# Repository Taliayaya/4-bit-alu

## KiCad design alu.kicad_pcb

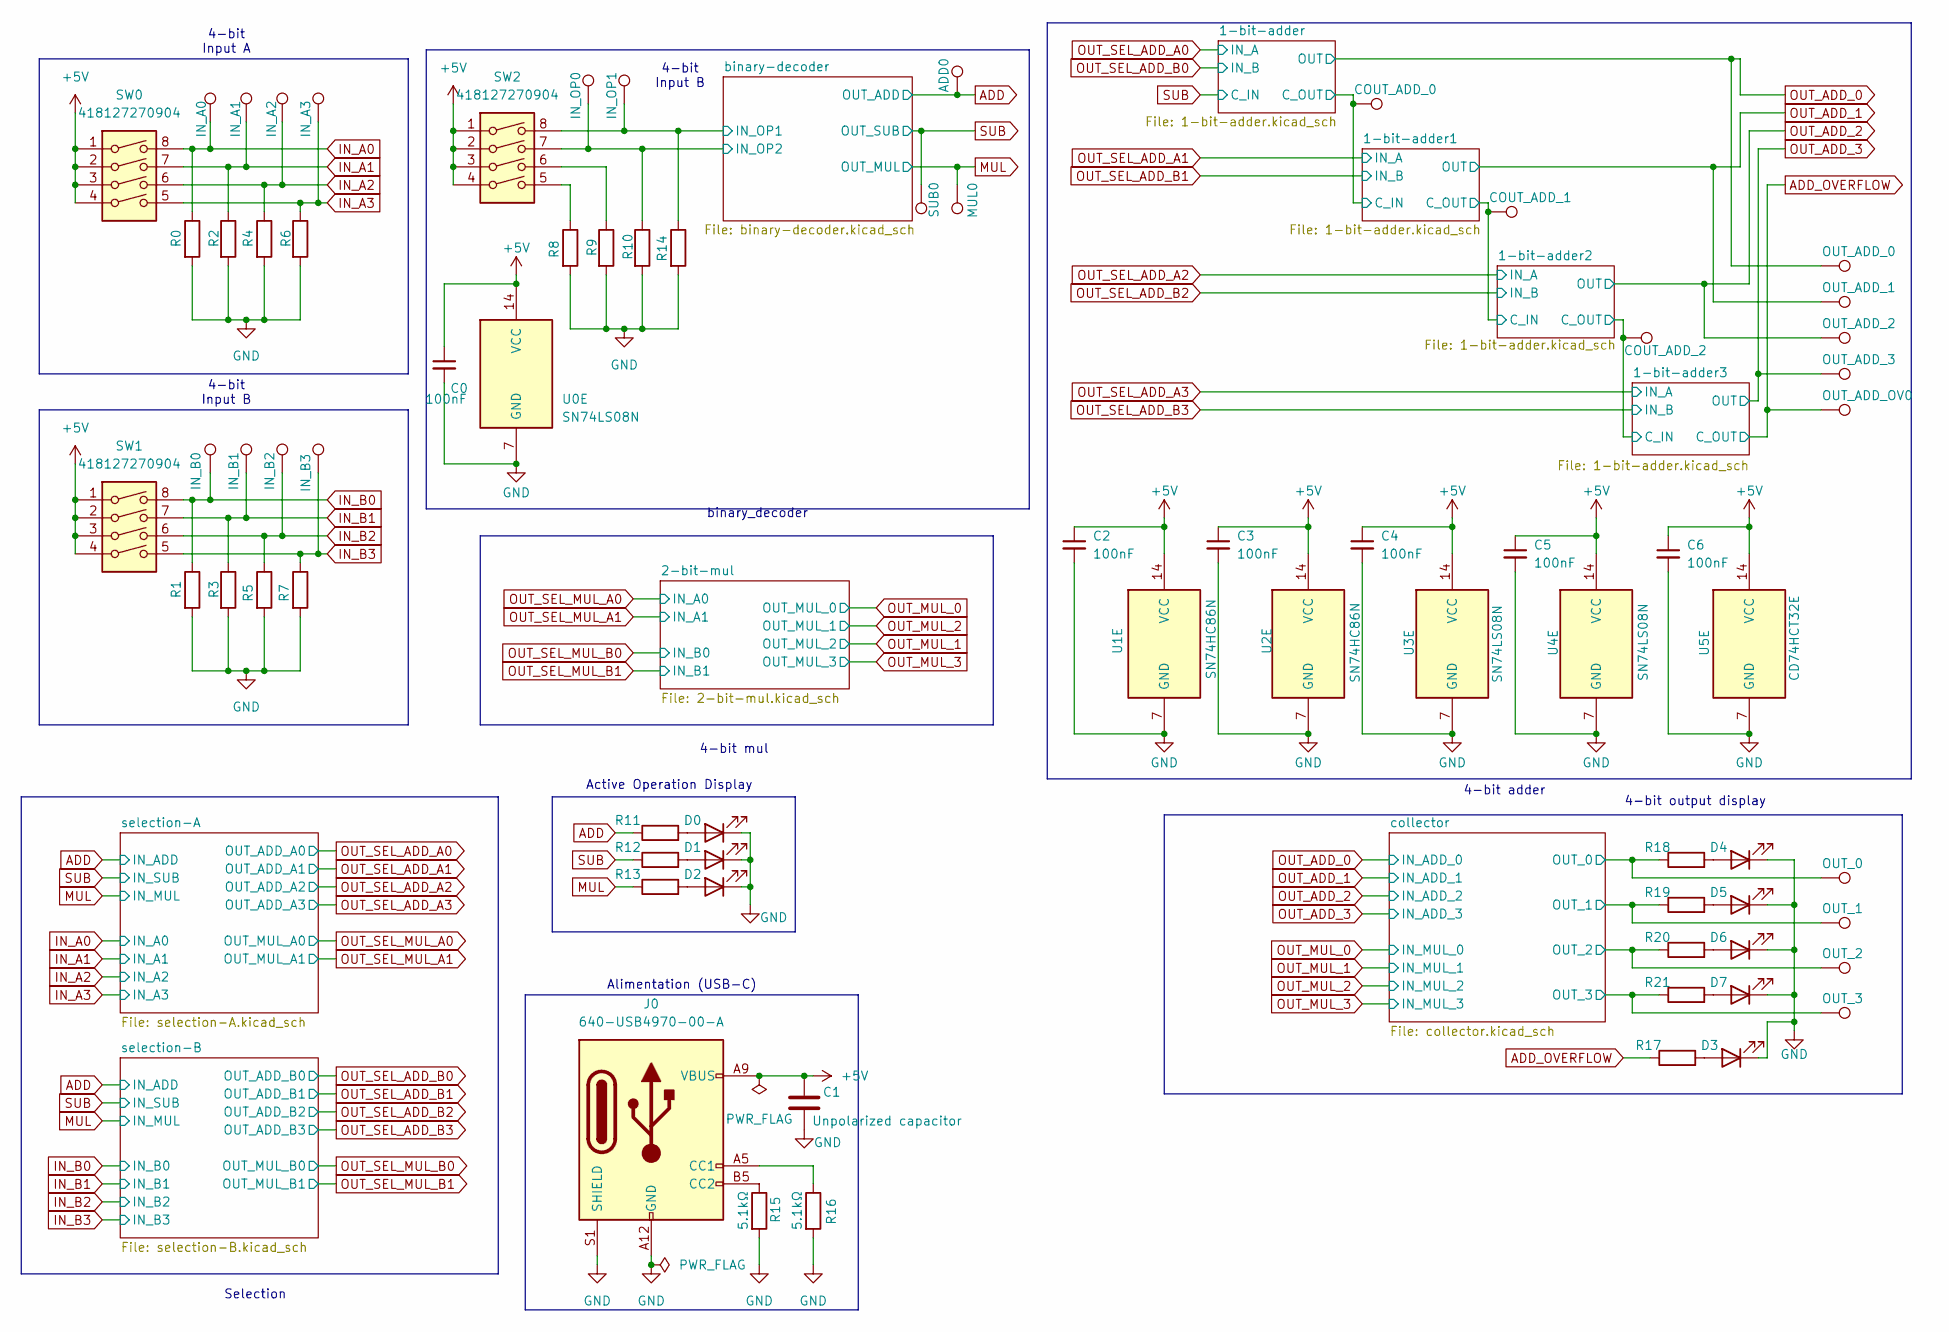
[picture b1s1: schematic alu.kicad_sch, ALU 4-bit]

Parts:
ADD0: TestPoint; TestPoint_THTPad_D1.0mm_Drill0.5mm
C0, C2, C3, C4, C5, C6: 100nF; C_0603_1608Metric
C1: 10uF; C_0603_1608Metric_Pad1.08x0.95mm_HandSolder
COUT_ADD_0, COUT_ADD_1, COUT_ADD_2: TestPoint; TestPoint_THTPad_D1.0mm_Drill0.5mm
D0, D1, D2, D3, D4, D5, D6, D7: 150080RS75000; LED_0805_2012Metric
IN_A0, IN_A1, IN_A2, IN_A3: TestPoint; TestPoint_THTPad_D1.0mm_Drill0.5mm
IN_B0, IN_B1, IN_B2, IN_B3: TestPoint; TestPoint_THTPad_D1.0mm_Drill0.5mm
IN_OP0, IN_OP1: TestPoint; TestPoint_THTPad_D1.0mm_Drill0.5mm
J0: 640-USB4970-00-A; USB_C_Receptacle_GCT_USB4125-xx-x_6P_TopMnt_Horizontal
MUL0: TestPoint; TestPoint_THTPad_D1.0mm_Drill0.5mm
OUT_0, OUT_1, OUT_2, OUT_3: TestPoint; TestPoint_THTPad_D1.0mm_Drill0.5mm
OUT_ADD_0, OUT_ADD_1, OUT_ADD_2, OUT_ADD_3: TestPoint; TestPoint_THTPad_D1.0mm_Drill0.5mm
OUT_ADD_OV0: TestPoint; TestPoint_THTPad_D1.0mm_Drill0.5mm
R0, R1, R2, R3, R4, R5, R6, R7, R8, R9, R10, R14: 10kΩ; R_0603_1608Metric_Pad0.98x0.95mm_HandSolder
R11, R12, R13, R17, R18, R19, R20, R21: 220Ω; R_0603_1608Metric_Pad0.98x0.95mm_HandSolder
R15, R16: 5.1kΩ; R_0603_1608Metric_Pad0.98x0.95mm_HandSolder
SUB0: TestPoint; TestPoint_THTPad_D1.0mm_Drill0.5mm
SW0, SW1, SW2: 418127270904; SW_DIP_SPSTx04_Slide_6.7x11.72mm_W7.62mm_P2.54mm_LowProfile
U0, U3, U4: SN74LS08N; DIP-14_W7.62mm_LongPads
U1, U2: SN74HC86N; DIP-14_W7.62mm_LongPads
U5: CD74HCT32E; DIP-14_W7.62mm_LongPads

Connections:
+5V: C0.1, C1.1, C2.1, C3.1, C4.1, C5.1, C6.1, J0.A9 (VBUS), J0.B9 (VBUS), SW0.1, SW0.2, SW0.3, SW0.4, SW1.1, SW1.2, SW1.3, SW1.4, SW2.1, SW2.2, SW2.3, SW2.4, U0.14 (VCC), U1.14 (VCC), U2.14 (VCC), U3.14 (VCC), U4.14 (VCC), U5.14 (VCC); also elsewhere on the board
/1-bit-adder1/C_OUT: COUT_ADD_1.1, U5.6; also elsewhere on the board
/1-bit-adder2/C_OUT: COUT_ADD_2.1, U2.13, U3.12, U5.8
/1-bit-adder/C_OUT: COUT_ADD_0.1, U0.12, U1.13; also elsewhere on the board
/binary-decoder/IN_OP1: IN_OP1.1, R14.1, SW2.8; also elsewhere on the board
/binary-decoder/IN_OP2: IN_OP0.1, R10.1, SW2.7; also elsewhere on the board
/collector/OUT_0: OUT_0.1, R18.1; also elsewhere on the board
/collector/OUT_1: OUT_1.1, R19.1; also elsewhere on the board
/collector/OUT_2: OUT_2.1, R20.1; also elsewhere on the board
/collector/OUT_3: OUT_3.1, R21.1; also elsewhere on the board
ADD: ADD0.1, R11.1; also elsewhere on the board
ADD_OVERFLOW: OUT_ADD_OV0.1, R17.1, U5.11
GND: C0.2, C1.2, C2.2, C3.2, C4.2, C5.2, C6.2, D0.1 (K), D1.1 (K), D2.1 (K), D3.1 (K), D4.1 (K), D5.1 (K), D6.1 (K), D7.1 (K), J0.A12 (GND), J0.B12 (GND), J0.S1 (SHIELD), R0.2, R1.2, R2.2, R3.2, R4.2, R5.2, R6.2, R7.2, R8.2, R9.2, R10.2, R14.2, R15.2, R16.2, U0.7 (GND), U1.7 (GND), U2.7 (GND), U3.7 (GND), U4.7 (GND), U5.7 (GND); also elsewhere on the board
IN_A0: IN_A0.1, R0.1, SW0.8; also elsewhere on the board
IN_A1: IN_A1.1, R2.1, SW0.7; also elsewhere on the board
IN_A2: IN_A2.1, R4.1, SW0.6; also elsewhere on the board
IN_A3: IN_A3.1, R6.1, SW0.5; also elsewhere on the board
IN_B0: IN_B0.1, R1.1, SW1.8; also elsewhere on the board
IN_B1: IN_B1.1, R3.1, SW1.7; also elsewhere on the board
IN_B2: IN_B2.1, R5.1, SW1.6; also elsewhere on the board
IN_B3: IN_B3.1, R7.1, SW1.5; also elsewhere on the board
MUL: MUL0.1, R13.1; also elsewhere on the board
unnamed: D0.2 (A), R11.2
unnamed: D1.2 (A), R12.2
unnamed: D2.2 (A), R13.2
unnamed: D3.2 (A), R17.2
unnamed: D4.2 (A), R18.2
unnamed: D5.2 (A), R19.2
unnamed: D6.2 (A), R20.2
unnamed: D7.2 (A), R21.2
unnamed: J0.A5 (CC1), R16.1
unnamed: J0.B5 (CC2), R15.1
unnamed: R8.1, SW2.5
unnamed: R9.1, SW2.6
unnamed: U0.8, U5.4
unnamed: U0.11, U5.5
unnamed: U0.13, U1.8, U1.12
unnamed: U2.8, U2.12, U3.13
unnamed 48: U5.9; also elsewhere on the board
unnamed 49: U5.10; also elsewhere on the board
unnamed: U3.8, U5.12
unnamed: U3.11, U5.13
OUT_ADD_0: OUT_ADD_0.1; also elsewhere on the board
OUT_ADD_1: OUT_ADD_1.1, U1.11; also elsewhere on the board
OUT_ADD_2: OUT_ADD_2.1; also elsewhere on the board
OUT_ADD_3: OUT_ADD_3.1, U2.11; also elsewhere on the board
OUT_SEL_ADD_A1: U0.9, U1.9; also elsewhere on the board
OUT_SEL_ADD_A3: U2.9, U3.9; also elsewhere on the board
OUT_SEL_ADD_B1: U0.10, U1.10; also elsewhere on the board
OUT_SEL_ADD_B3: U2.10, U3.10; also elsewhere on the board
SUB: R12.1, SUB0.1; also elsewhere on the board

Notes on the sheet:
Alimentation (USB-C)
4-bit output display
Active Operation Display
4-bit Input A
Selection
4-bit Input B
4-bit mul
binary_decoder
4-bit adder

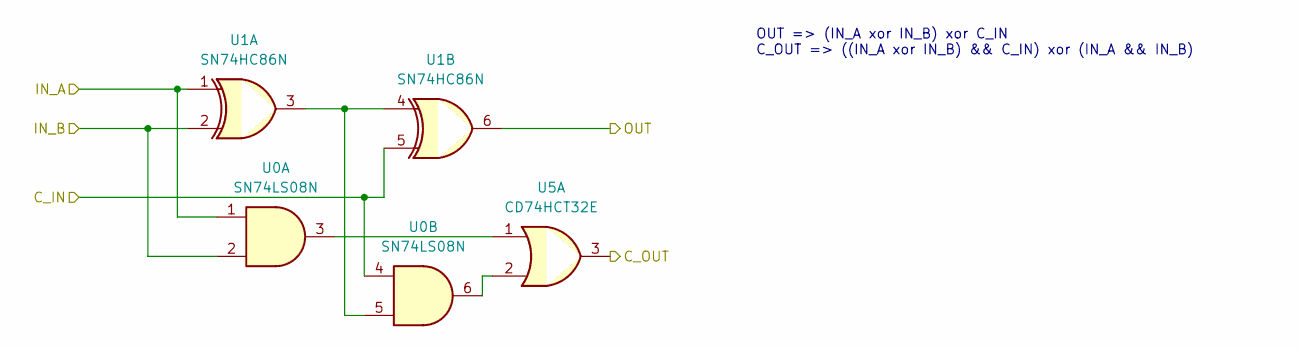
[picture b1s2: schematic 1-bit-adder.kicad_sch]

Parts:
U0: SN74LS08N; DIP-14_W7.62mm_LongPads
U1: SN74HC86N; DIP-14_W7.62mm_LongPads
U5: CD74HCT32E; DIP-14_W7.62mm_LongPads

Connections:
/1-bit-adder1/C_OUT: U5.6; also elsewhere on the board
/1-bit-adder2/C_OUT: U5.8; also elsewhere on the board
/1-bit-adder/C_OUT: U0.12, U1.13, U5.3; also elsewhere on the board
ADD_OVERFLOW: U5.11; also elsewhere on the board
unnamed: U0.3, U5.1
unnamed: U0.5, U1.3, U1.4
unnamed: U0.6, U5.2
unnamed: U0.8, U5.4
unnamed: U0.11, U5.5
unnamed: U0.13, U1.8, U1.12
unnamed 48: U5.9; also elsewhere on the board
unnamed 49: U5.10; also elsewhere on the board
unnamed 50: U5.12; also elsewhere on the board
unnamed 51: U5.13; also elsewhere on the board
OUT_ADD_0: U1.6; also elsewhere on the board
OUT_ADD_1: U1.11; also elsewhere on the board
OUT_SEL_ADD_A0: U0.1, U1.1; also elsewhere on the board
OUT_SEL_ADD_A1: U0.9, U1.9; also elsewhere on the board
OUT_SEL_ADD_B0: U0.2, U1.2; also elsewhere on the board
OUT_SEL_ADD_B1: U0.10, U1.10; also elsewhere on the board
SUB: U0.4, U1.5; also elsewhere on the board

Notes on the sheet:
OUT => (IN_A xor IN_B) xor C_IN C_OUT => ((IN_A xor IN_B) && C_IN) xor (IN_A && IN_B)

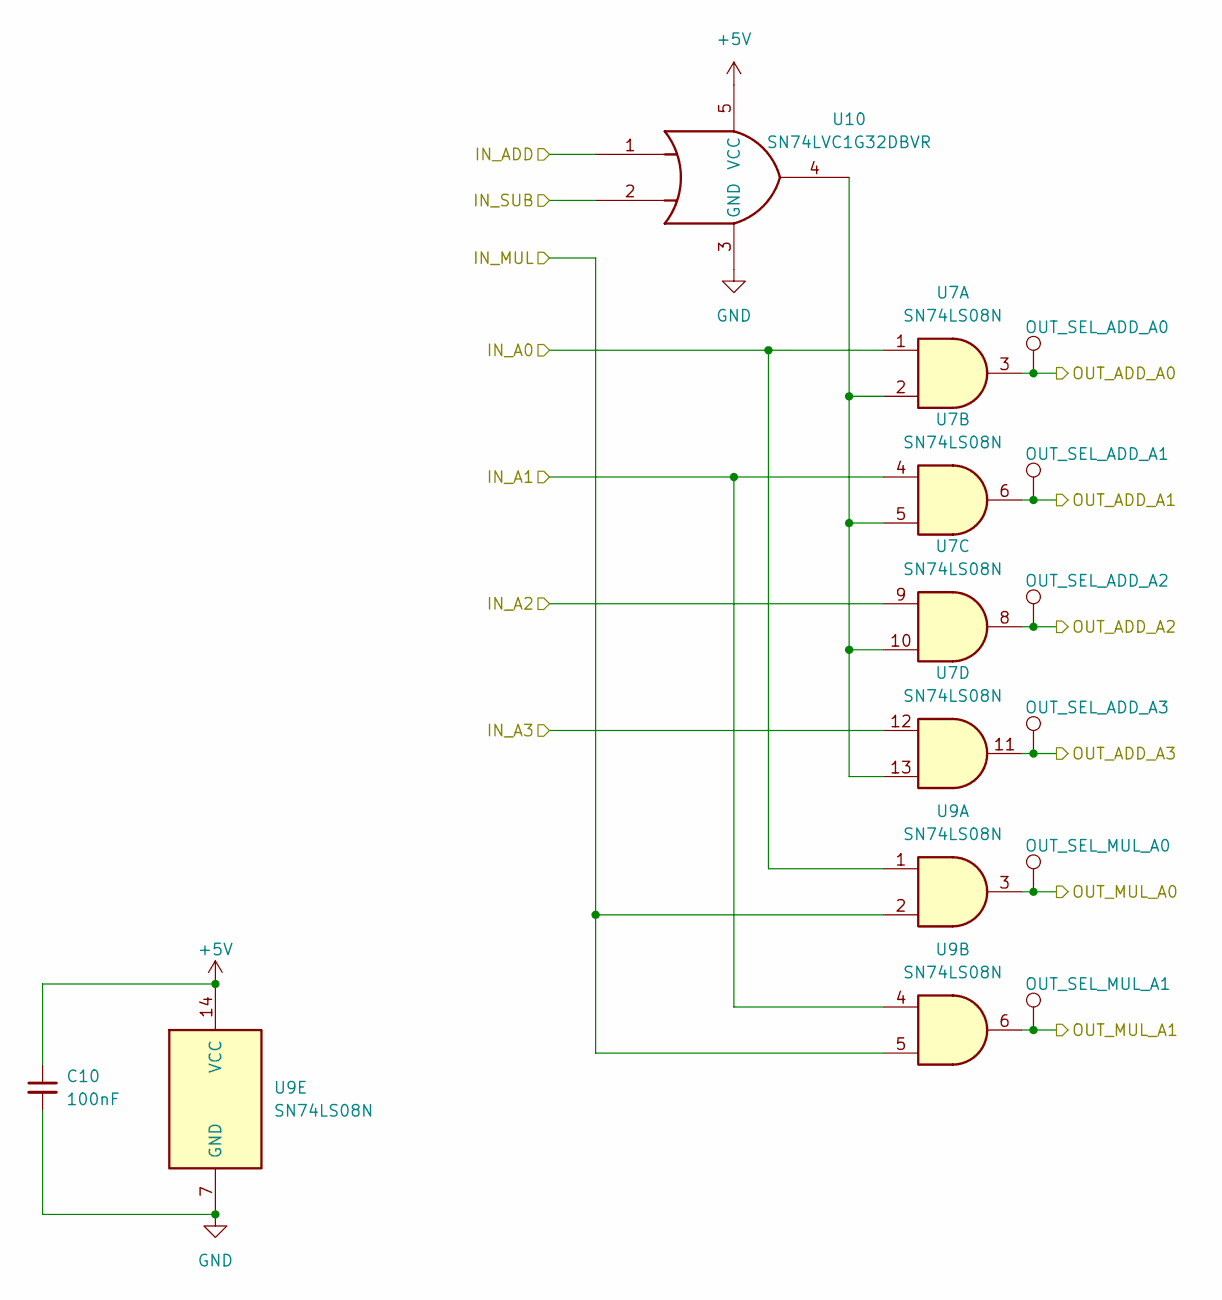
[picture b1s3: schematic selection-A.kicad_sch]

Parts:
C10: 100nF; C_0603_1608Metric
OUT_SEL_ADD_A0, OUT_SEL_ADD_A1, OUT_SEL_ADD_A2, OUT_SEL_ADD_A3: TestPoint; TestPoint_THTPad_D1.0mm_Drill0.5mm
OUT_SEL_MUL_A0, OUT_SEL_MUL_A1: TestPoint; TestPoint_THTPad_D1.0mm_Drill0.5mm
U7, U9: SN74LS08N; DIP-14_W7.62mm_LongPads
U10: SN74LVC1G32DBVR; SOT-23-5_HandSoldering

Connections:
+5V: C10.1, U9.14 (VCC), U10.5 (VCC); also elsewhere on the board
ADD: U10.1; also elsewhere on the board
GND: C10.2, U9.7 (GND), U10.3 (GND); also elsewhere on the board
IN_A0: U7.1, U9.1; also elsewhere on the board
IN_A1: U7.4, U9.4; also elsewhere on the board
IN_A2: U7.9; also elsewhere on the board
IN_A3: U7.12; also elsewhere on the board
MUL: U9.2, U9.5; also elsewhere on the board
unnamed: U7.2, U7.5, U7.10, U7.13, U10.4
OUT_SEL_ADD_A0: OUT_SEL_ADD_A0.1, U7.3; also elsewhere on the board
OUT_SEL_ADD_A1: OUT_SEL_ADD_A1.1, U7.6; also elsewhere on the board
OUT_SEL_ADD_A2: OUT_SEL_ADD_A2.1, U7.8; also elsewhere on the board
OUT_SEL_ADD_A3: OUT_SEL_ADD_A3.1, U7.11; also elsewhere on the board
OUT_SEL_MUL_A0: OUT_SEL_MUL_A0.1, U9.3; also elsewhere on the board
OUT_SEL_MUL_A1: OUT_SEL_MUL_A1.1, U9.6; also elsewhere on the board
SUB: U10.2; also elsewhere on the board

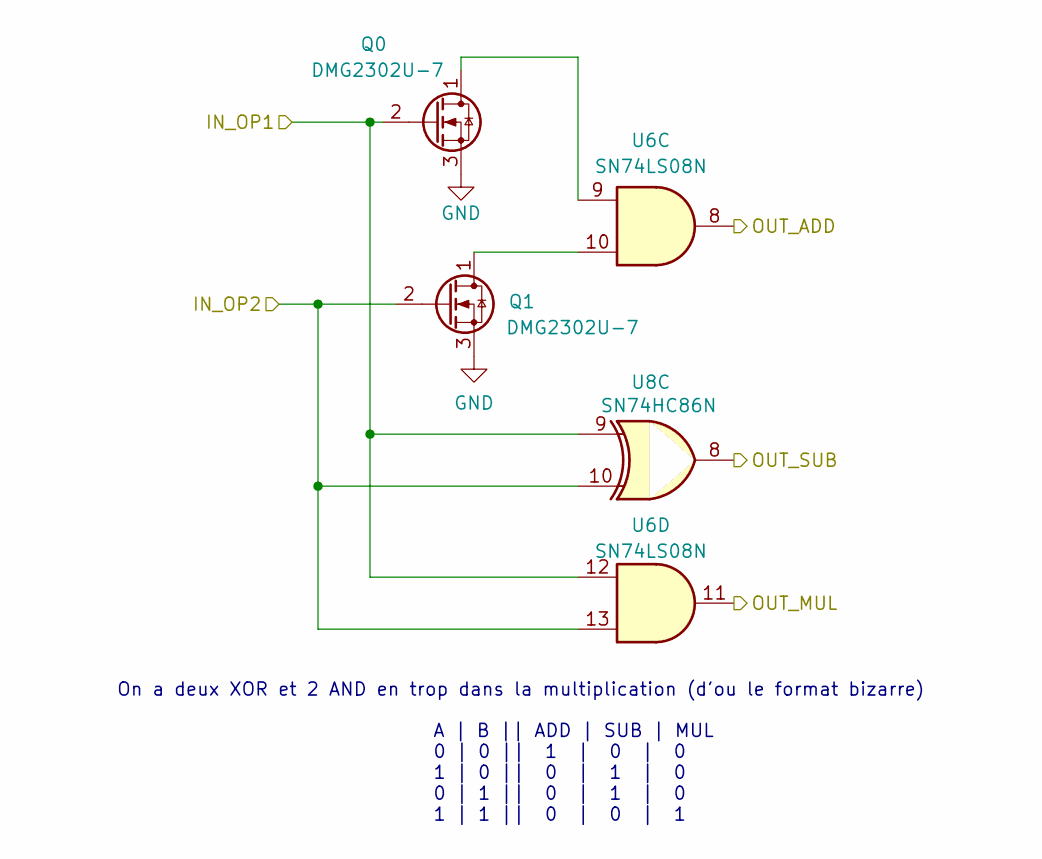
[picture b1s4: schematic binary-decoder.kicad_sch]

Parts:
Q0, Q1: DMG2302U-7; SOT-23-3
U6: SN74LS08N; DIP-14_W7.62mm_LongPads
U8: SN74HC86N; DIP-14_W7.62mm_LongPads

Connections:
/binary-decoder/IN_OP1: Q0.2 (G), U6.12, U8.9; also elsewhere on the board
/binary-decoder/IN_OP2: Q1.2 (G), U6.13, U8.10; also elsewhere on the board
ADD: U6.8; also elsewhere on the board
GND: Q0.3 (S), Q1.3 (S); also elsewhere on the board
MUL: U6.11; also elsewhere on the board
unnamed 32: Q0.1 (D), U6.9; also elsewhere on the board
unnamed 33: Q1.1 (D), U6.10; also elsewhere on the board
SUB: U8.8; also elsewhere on the board

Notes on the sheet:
A | B || ADD | SUB | MUL 0 | 0 || 1 | 0 | 0 1 | 0 || 0 | 1 | 0 0 | 1 || 0 | 1 | 0 1 | 1 || 0 | 0 | 1
On a deux XOR et 2 AND en trop dans la multiplication (d'ou le format bizarre)

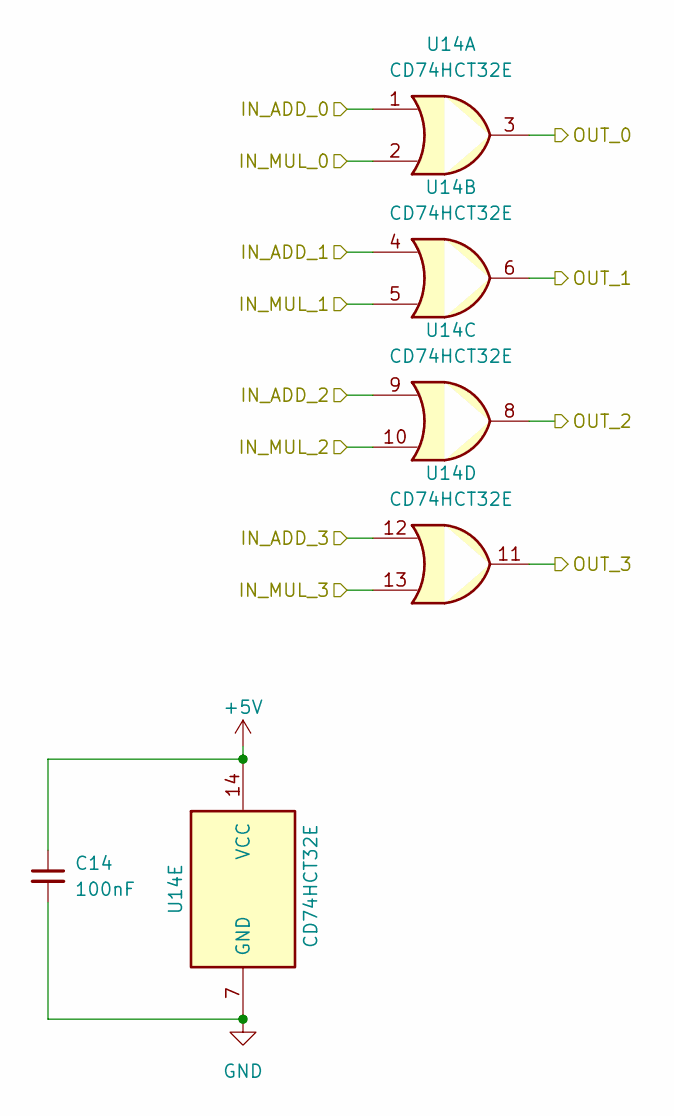
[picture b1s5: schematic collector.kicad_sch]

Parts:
C14: 100nF; C_0603_1608Metric
U14: CD74HCT32E; DIP-14_W7.62mm_LongPads

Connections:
+5V: C14.1, U14.14 (VCC); also elsewhere on the board
/collector/OUT_0: U14.3; also elsewhere on the board
/collector/OUT_1: U14.6; also elsewhere on the board
/collector/OUT_2: U14.8; also elsewhere on the board
/collector/OUT_3: U14.11; also elsewhere on the board
GND: C14.2, U14.7 (GND); also elsewhere on the board
OUT_ADD_0: U14.1; also elsewhere on the board
OUT_ADD_1: U14.4; also elsewhere on the board
OUT_ADD_2: U14.9; also elsewhere on the board
OUT_ADD_3: U14.12; also elsewhere on the board
OUT_MUL_0: U14.2; also elsewhere on the board
OUT_MUL_1: U14.5; also elsewhere on the board
OUT_MUL_2: U14.10; also elsewhere on the board
OUT_MUL_3: U14.13; also elsewhere on the board

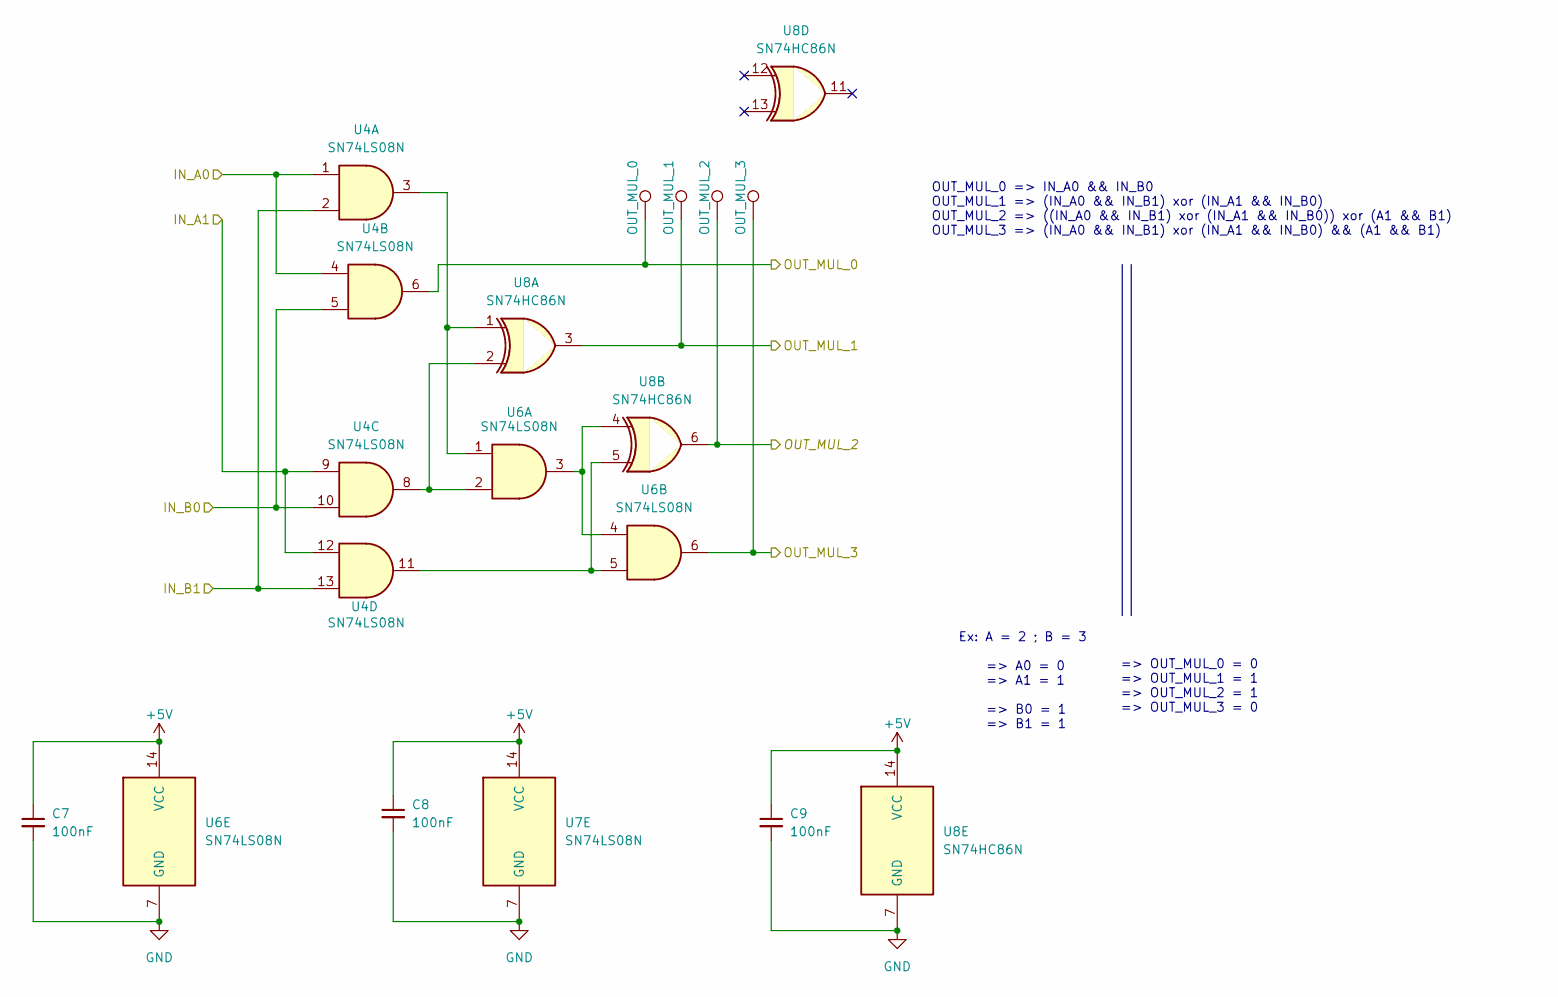
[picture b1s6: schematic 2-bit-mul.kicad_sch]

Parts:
C7, C8, C9: 100nF; C_0603_1608Metric
OUT_MUL_0, OUT_MUL_1, OUT_MUL_2, OUT_MUL_3: TestPoint; TestPoint_THTPad_D1.0mm_Drill0.5mm
U4, U6, U7: SN74LS08N; DIP-14_W7.62mm_LongPads
U8: SN74HC86N; DIP-14_W7.62mm_LongPads

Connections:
+5V: C7.1, C8.1, C9.1, U6.14 (VCC), U7.14 (VCC), U8.14 (VCC); also elsewhere on the board
GND: C7.2, C8.2, C9.2, U6.7 (GND), U7.7 (GND), U8.7 (GND); also elsewhere on the board
unnamed: U4.3, U6.1, U8.1
unnamed: U4.8, U6.2, U8.2
unnamed: U4.11, U6.5, U8.5
unnamed: U6.3, U6.4, U8.4
OUT_MUL_0: OUT_MUL_0.1, U4.6; also elsewhere on the board
OUT_MUL_1: OUT_MUL_2.1, U8.6; also elsewhere on the board
OUT_MUL_2: OUT_MUL_1.1, U8.3; also elsewhere on the board
OUT_MUL_3: OUT_MUL_3.1, U6.6; also elsewhere on the board
OUT_SEL_MUL_A0: U4.1, U4.4; also elsewhere on the board
OUT_SEL_MUL_A1: U4.9, U4.12; also elsewhere on the board
OUT_SEL_MUL_B0: U4.5, U4.10; also elsewhere on the board
OUT_SEL_MUL_B1: U4.2, U4.13; also elsewhere on the board

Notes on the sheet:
OUT_MUL_0 => IN_A0 && IN_B0 OUT_MUL_1 => (IN_A0 && IN_B1) xor (IN_A1 && IN_B0) OUT_MUL_2 => ((IN_A0 && IN_B1) xor (IN_A1 && IN_B0)) xor (A1 && B1) OUT_MUL_3 => (IN_A0 && IN_B1) xor (IN_A1 && IN_B0) && (A1 && B1)
=> OUT_MUL_0 = 0 => OUT_MUL_1 = 1 => OUT_MUL_2 = 1 => OUT_MUL_3 = 0
Ex: A = 2 ; B = 3 => A0 = 0 => A1 = 1 => B0 = 1 => B1 = 1

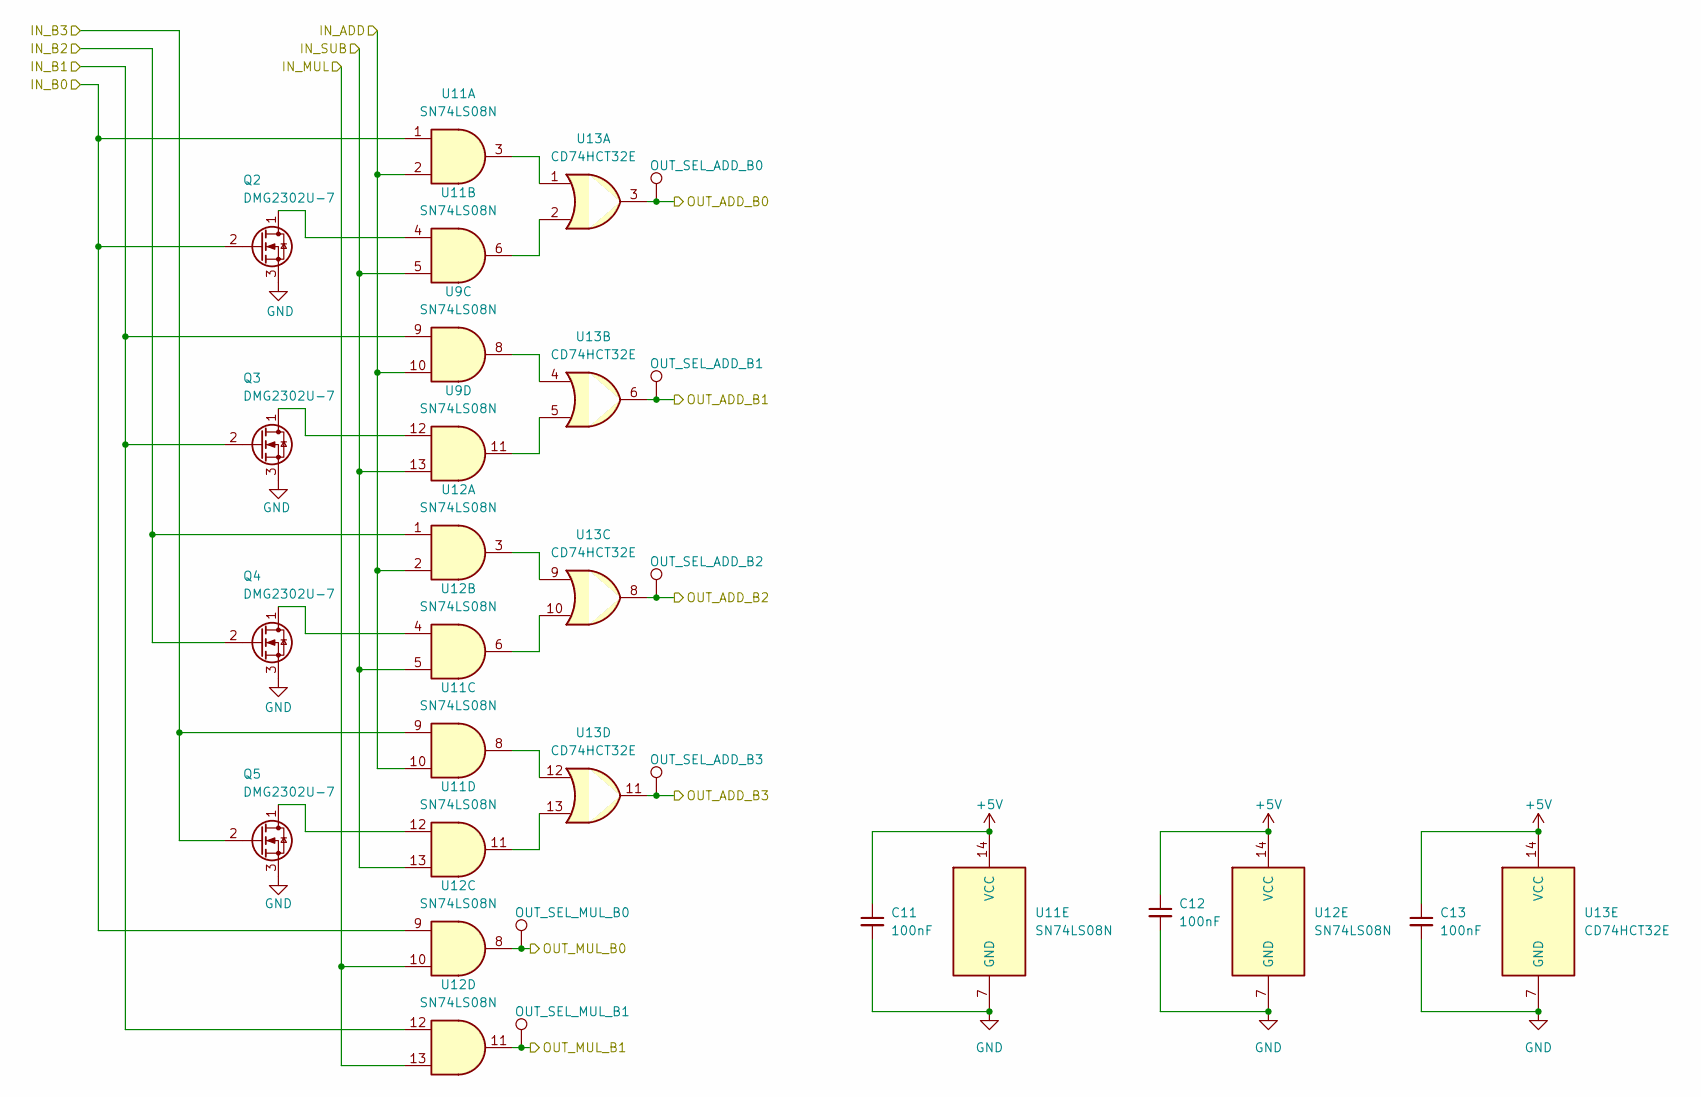
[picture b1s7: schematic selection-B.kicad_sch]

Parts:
C11, C12, C13: 100nF; C_0603_1608Metric
OUT_SEL_ADD_B0, OUT_SEL_ADD_B1, OUT_SEL_ADD_B2, OUT_SEL_ADD_B3: TestPoint; TestPoint_THTPad_D1.0mm_Drill0.5mm
OUT_SEL_MUL_B0, OUT_SEL_MUL_B1: TestPoint; TestPoint_THTPad_D1.0mm_Drill0.5mm
Q2, Q3, Q4, Q5: DMG2302U-7; SOT-23-3
U9, U11, U12: SN74LS08N; DIP-14_W7.62mm_LongPads
U13: CD74HCT32E; DIP-14_W7.62mm_LongPads

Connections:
+5V: C11.1, C12.1, C13.1, U11.14 (VCC), U12.14 (VCC), U13.14 (VCC); also elsewhere on the board
ADD: U9.10, U11.2, U11.10, U12.2; also elsewhere on the board
GND: C11.2, C12.2, C13.2, Q2.3 (S), Q3.3 (S), Q4.3 (S), Q5.3 (S), U11.7 (GND), U12.7 (GND), U13.7 (GND); also elsewhere on the board
IN_B0: Q2.2 (G), U11.1, U12.9; also elsewhere on the board
IN_B1: Q3.2 (G), U9.9, U12.12; also elsewhere on the board
IN_B2: Q4.2 (G), U12.1; also elsewhere on the board
IN_B3: Q5.2 (G), U11.9; also elsewhere on the board
MUL: U12.10, U12.13; also elsewhere on the board
unnamed 34: Q2.1 (D), U11.4; also elsewhere on the board
unnamed 35: Q3.1 (D), U9.12; also elsewhere on the board
unnamed 36: Q4.1 (D), U12.4; also elsewhere on the board
unnamed 37: Q5.1 (D), U11.12; also elsewhere on the board
unnamed: U11.3, U13.1
unnamed: U11.6, U13.2
unnamed: U11.8, U13.12
unnamed: U11.11, U13.13
unnamed: U12.3, U13.9
unnamed: U12.6, U13.10
unnamed: U9.8, U13.4
unnamed: U9.11, U13.5
OUT_SEL_ADD_B0: OUT_SEL_ADD_B0.1, U13.3; also elsewhere on the board
OUT_SEL_ADD_B1: OUT_SEL_ADD_B1.1, U13.6; also elsewhere on the board
OUT_SEL_ADD_B2: OUT_SEL_ADD_B2.1, U13.8; also elsewhere on the board
OUT_SEL_ADD_B3: OUT_SEL_ADD_B3.1, U13.11; also elsewhere on the board
OUT_SEL_MUL_B0: OUT_SEL_MUL_B0.1, U12.8; also elsewhere on the board
OUT_SEL_MUL_B1: OUT_SEL_MUL_B1.1, U12.11; also elsewhere on the board
SUB: U9.13, U11.5, U11.13, U12.5; also elsewhere on the board

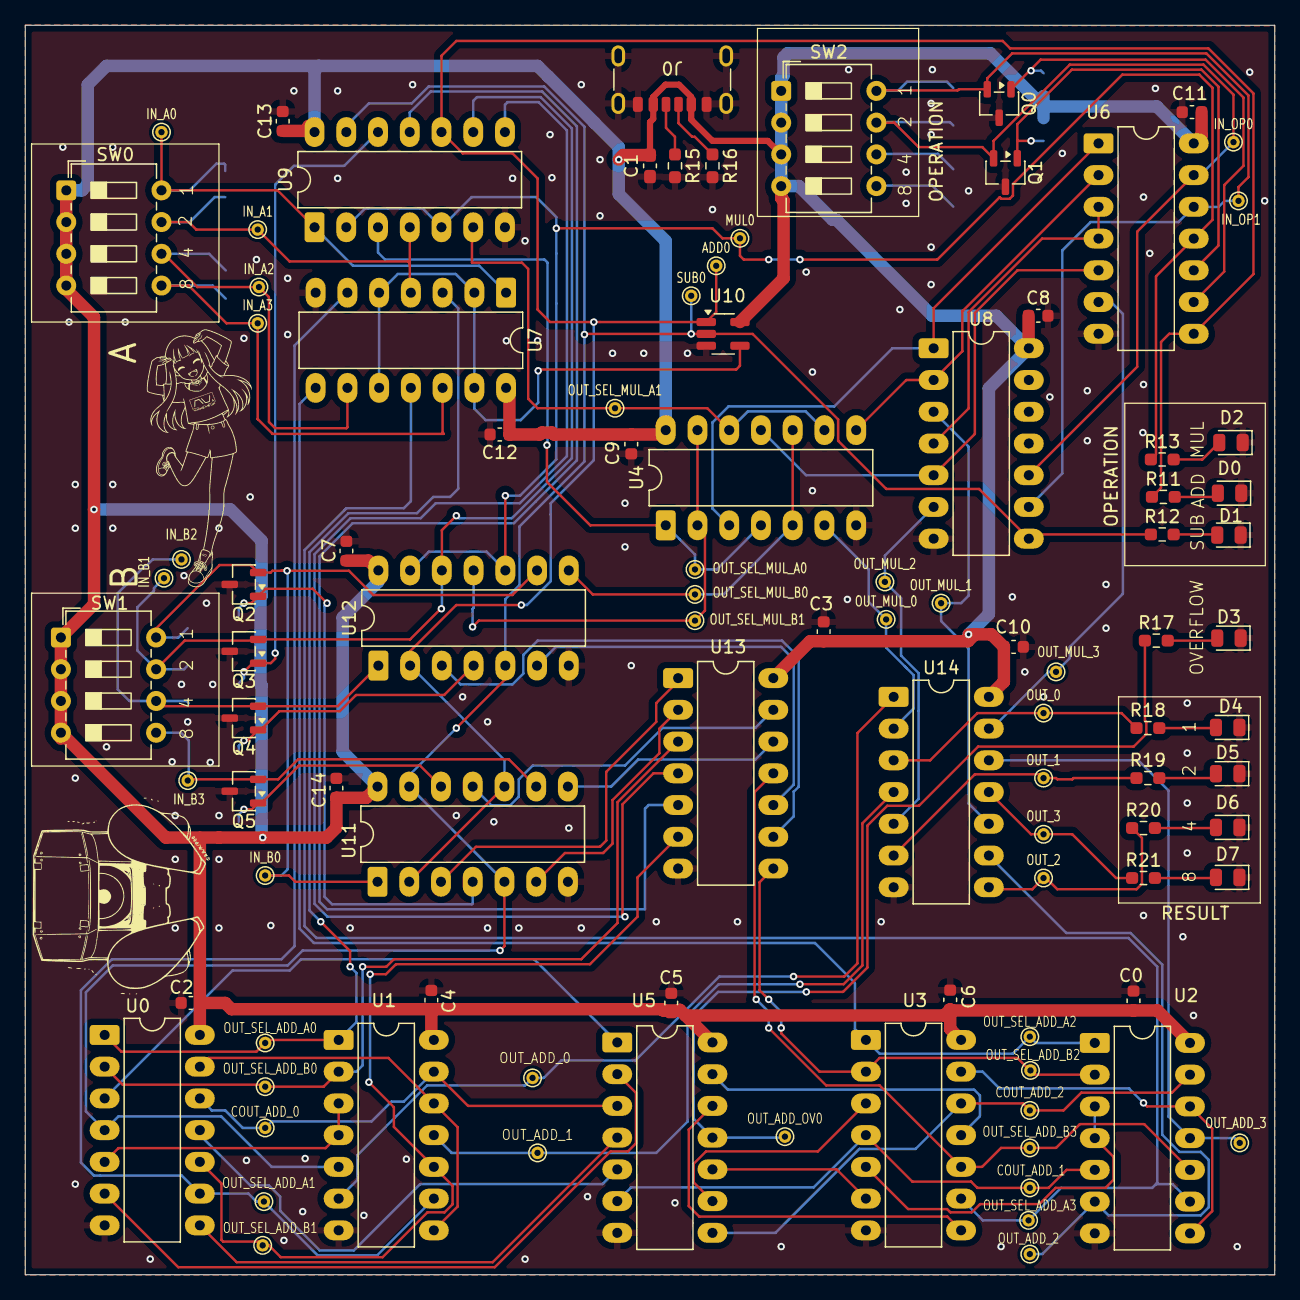
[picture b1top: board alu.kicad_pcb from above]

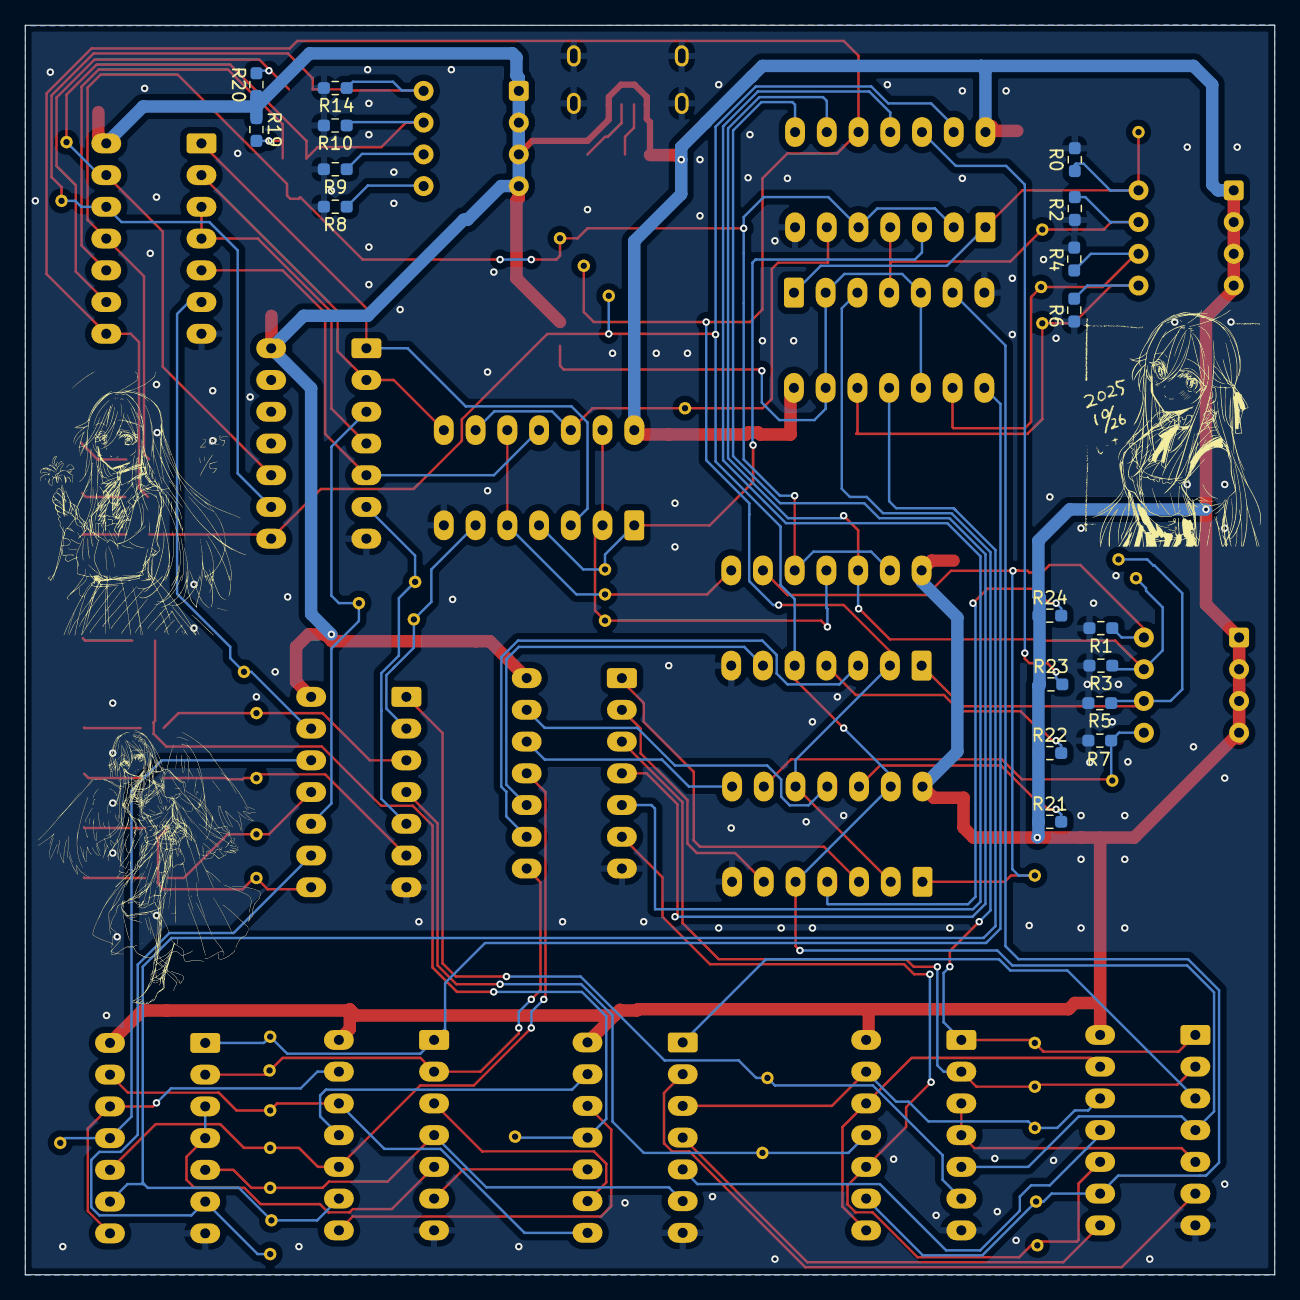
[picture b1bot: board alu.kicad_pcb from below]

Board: 2 copper layers, 100.0 x 100.0 mm, 117 parts (18 on the bottom side), 86 nets.

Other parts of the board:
R19#2, R20#2, R21#2, R22, R23, R24: 10k; R_0603_1608Metric_Pad0.98x0.95mm_HandSolder

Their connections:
+5V: R19#2.1, R20#2.1, R21#2.1, R22.1, R23.1, R24.1; also elsewhere on the board
unnamed 32: R20#2.2; also elsewhere on the board
unnamed 33: R19#2.2; also elsewhere on the board
unnamed 34: R24.2; also elsewhere on the board
unnamed 35: R23.2; also elsewhere on the board
unnamed 36: R22.2; also elsewhere on the board
unnamed 37: R21#2.2; also elsewhere on the board

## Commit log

2026-03-02 feat: init
2026-03-02 feat: 4-bit adder
2026-03-02 feat: working 4-bit adder (normally)
2026-03-02 feat: mul
2026-03-03 feat(mul): clean version
2026-03-03 fix(mul): typo in output label
2026-03-04 sync
2026-03-04 feat: removed ERC errors
2026-03-04 Add stuff and fix rce errors (#1)
    * sync
    * feat: removed ERC errors
2026-03-04 fix: removed ERC warnings and errors
2026-03-04 chore: move stuff around
2026-03-23 feat: NOT to mofset + first batch of footprint
2026-03-25 feat: added footprint for mofsets
2026-03-25 feat: footprints on gates
2026-03-25 fix: save
2026-03-25 feat: updated footprint
2026-03-25 feat: usb c
2026-03-25 fix: updated footprint for mofset to 23-3 and switch to HandSoldering type
2026-03-25 fix: forgot to save before commit
2026-03-25 feat: added capacitor with footprint
2026-03-25 fix: merge
2026-03-25 fix: fixed capa
2026-03-25 fix: capacitor collector/add
2026-03-25 fix: annotation
2026-03-25 fix: fixed link of capas
2026-03-25 fix: 0 error 0 warning
2026-03-25 fix: change dip switch footprint
2026-03-25 feat: updated references
2026-03-26 feat: pcb layout position
2026-03-28 feat: pcb linkes swicthes
2026-03-28 fix: unfilled and refilles ground zone
2026-03-28 fix: fixed ground issue
2026-03-29 Routed bottom part of the PCB
2026-03-30 feat: all connected, 30+ errors remaining
2026-03-31 Remove capacitors + change R and C footprints + finish PCB routing
2026-04-02 feat: kicad 10 to kicad 9
2026-04-02 fix: reput capas -- where is my gift?
2026-04-02 feat: missing pull up
2026-04-02 fix: updated pcb with capas
2026-04-02 feat(pcb): pull up and 1mm 5v and 0 error/warning
2026-04-02 feat: multiplier schema
2026-04-02 fix: added binary table of adder
2026-04-02 feat: added op led
2026-04-02 feat: basic silk
2026-04-28 feat: added point_tests + fixed wrong footprint for switch + added anime girl
2026-04-28 fix: typos
2026-04-29 chore: changed R and C ref to passive value
2026-04-29 fix: added datasheets
2026-04-29 fix: chores pcb
2026-04-29 fix: fix
2026-04-29 feat: v1
